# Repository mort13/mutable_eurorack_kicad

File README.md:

Mutable Instruments' Eurorack Modules.

Forked from pichenettes' version and identical except:
- Eagle brd and sch files converted to XML (making possible import into KiCad)
- For some modules, KiCad versions have been added

I have updated this repo to reflect upstream changes, but I am no longer able to convert the Eagle files, so not all are available as XML.

* [Blades](http://mutable-instruments.net/modules/blades): Dual multimode filter.
* [Blinds](http://mutable-instruments.net/modules/blinds): Quad VC-polarizer.
* [Braids](http://mutable-instruments.net/modules/braids): Macro-oscillator.
* [Branches](http://mutable-instruments.net/modules/branches): Dual Bernoulli gate.
* [Clouds](http://mutable-instruments.net/modules/clouds): Texture synthesizer.
* [Ears](http://mutable-instruments.net/modules/ears): Contact microphone.
* [Edges](http://mutable-instruments.net/modules/edges): Quad chiptune digital oscillator.
* [Elements](http://mutable-instruments.net/modules/elements): Modal synthesizer.
* [Frames](http://mutable-instruments.net/modules/frames): Keyframer/mixer.
* [Grids](http://mutable-instruments.net/modules/grids): Topographic drum sequencer.
* [Kinks](http://mutable-instruments.net/modules/kinks): Utility module - rectifier, analog logic, S&H, noise.
* [Links](http://mutable-instruments.net/modules/links): Utility module - buffer, mixer.
* [Marbles](http://mutable-instruments.net/modules/marbles): Random sampler.
* [Peaks](http://mutable-instruments.net/modules/peaks): Dual trigger converter.
* [Plaits](http://mutable-instruments.net/modules/plaits): Macro oscillator.
* [Rings](http://mutable-instruments.net/modules/rings): Resonator.
* [Ripples](http://mutable-instruments.net/modules/ripples): Liquid 2-pole BP, 2-pole LP and 4-pole LP filter.
* [Shades](http://mutable-instruments.net/modules/shades): Triple attenuverter.
* [Shelves](http://mutable-instruments.net/modules/shelves): EQ filter.
* [Stages](http://mutable-instruments.net/modules/stages): Segment generator.
* [Streams](http://mutable-instruments.net/modules/streams): Dual dynamics gate.
* [Tides](http://mutable-instruments.net/modules/tides): Tidal modulator.
* [Veils](http://mutable-instruments.net/modules/veils): Quad VCA.
* [Volts](http://mutable-instruments.net/modules/volts): +5V power module.
* [Warps](http://mutable-instruments.net/modules/warps): Meta-modulator.
* [Yarns](http://mutable-instruments.net/modules/yarns): MIDI interface.

License
=======

Code (AVR projects): GPL3.0.

Code (STM32F projects): MIT license.

Hardware: cc-by-sa-3.0

By: Emilie Gillet (emilie.o.gillet@gmail.com)

Guidelines for derivative works
===============================

**Mutable Instruments is a registered trademark.**

The name "Mutable Instruments" should not be used on any of the derivative works you create from these files.

We do not recommend you to keep the original name of the Mutable Instruments module for your derivative works.

For example, your 5U adaptation of Mutable Instruments Clouds can be called "Foobar Modular - Particle Generator".

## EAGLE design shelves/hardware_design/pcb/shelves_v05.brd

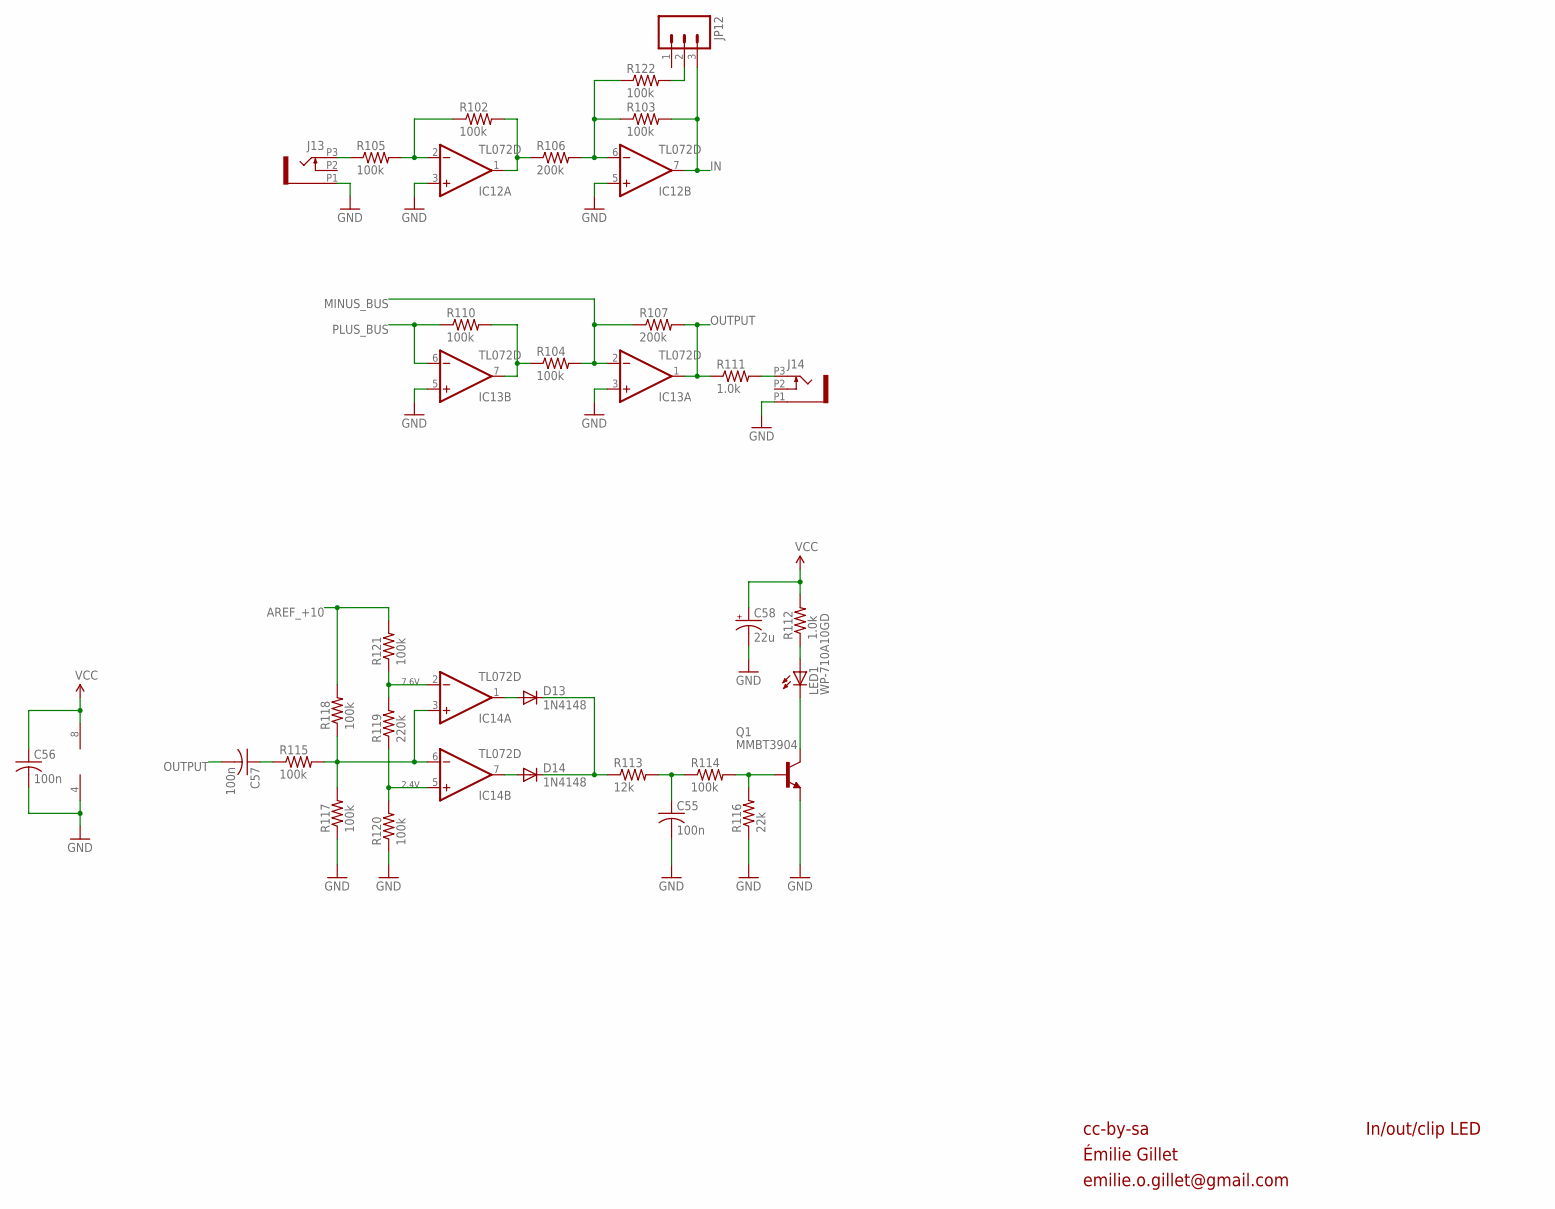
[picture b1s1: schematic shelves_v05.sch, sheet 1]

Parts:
C55, C56, C57: 100n; C0603
C58: 22u; PANASONIC_C
D13, D14: 1N4148; SOD323-W
IC12, IC13, IC14: TL072D; SO08
J13, J14: PJ301_THONKICONN6; WQP_PJ_301M6
JP12: M03PTH; 1X03
LED1: WP-710A10GD; LED3MM
Q1: MMBT3904; SOT23-BEC
R102, R103, R104, R105, R110, R114, R115, R117, R118, R120, R121, R122: 100k; R0603
R106, R107: 200k; R0603
R111, R112: 1.0k; R0603
R113: 12k; R0603
R116: 22k; R0603
R119: 220k; R0603

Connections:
AREF_+10: R118.2, R121.2; also elsewhere on the board
GND: C55.2, C56.2, C58.-, IC12.3 (+IN), IC12.5 (+IN), IC13.3 (+IN), IC13.5 (+IN), IC14.4 (V-), J13.P1 (1), J14.P1 (1), Q1.E, R116.1, R117.1, R120.1; also elsewhere on the board
IN: IC12.7 (OUT), JP12.3, R103.2; also elsewhere on the board
IN_INV: IC12.1 (OUT), R102.2, R106.1
IN_INV1: IC13.7 (OUT), R104.1, R110.2
J_IN: J13.P3 (3), R105.1
MINUS_BUS: IC13.2 (-IN), R104.2, R107.1; also elsewhere on the board
unnamed: JP12.2, R122.2
unnamed: IC12.2 (-IN), R102.1, R105.2
unnamed: IC12.6 (-IN), R103.1, R106.2, R122.1
unnamed: LED1.K (C), Q1.C
unnamed: J14.P3 (3), R111.2
unnamed: C57.1, R115.1
unnamed: IC14.3 (+IN), IC14.6 (-IN), R115.2, R117.2, R118.1
unnamed: IC14.2 (-IN), R119.2, R121.1
unnamed: C55.1, R113.2, R114.1
unnamed: IC14.5 (+IN), R119.1, R120.2
unnamed: D13.A, IC14.1 (OUT)
unnamed: D14.A, IC14.7 (OUT)
unnamed: D13.C, D14.C, R113.1
unnamed: LED1.A, R112.1
unnamed: Q1.B, R114.2, R116.2
OUTPUT: C57.2, IC13.1 (OUT), R107.2, R111.1
PLUS_BUS: IC13.6 (-IN), R110.1; also elsewhere on the board
VCC: C56.1, C58.+, IC14.8 (V+), R112.2; also elsewhere on the board

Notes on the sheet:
cc-by-sa
In/out/clip LED
2.4V
7.6V
Émilie Gillet
emilie.o.gillet@gmail.com

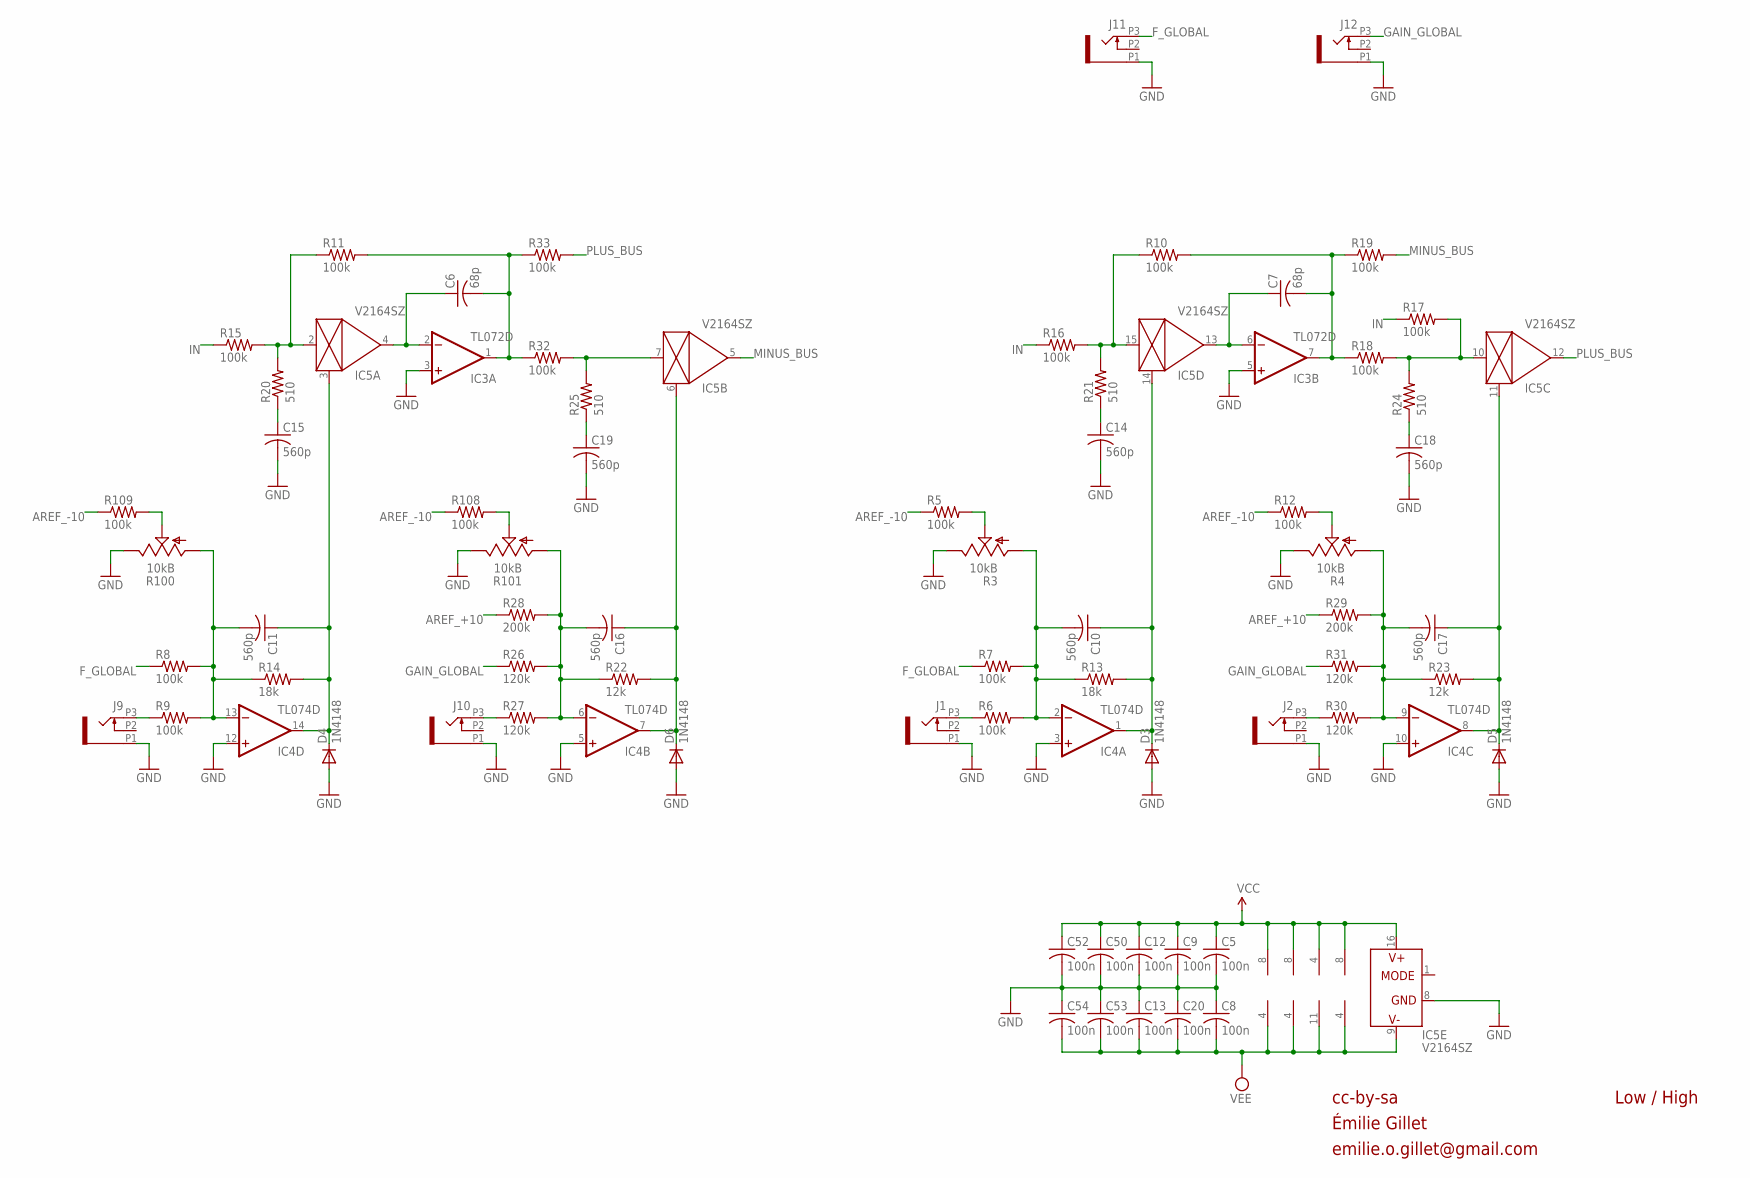
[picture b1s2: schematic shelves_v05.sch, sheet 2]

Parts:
C5, C8, C9, C12, C13, C20, C50, C52, C53, C54: 100n; C0603
C6, C7: 68p; C0603
C10, C11, C14, C15, C16, C17, C18, C19: 560p; C0603
D3, D4, D5, D6: 1N4148; SOD323-W
IC3, IC12, IC13: TL072D; SO08
IC4: TL074D; SO14
IC5: V2164SZ; SOIC16N
J1, J2, J9, J10, J11, J12: PJ301_THONKICONN6; WQP_PJ_301M6
R3, R4, R100, R101: 10kB; ALPS_POT_VERTICAL_PS
R5, R6, R7, R8, R9, R10, R11, R12, R15, R16, R17, R18, R19, R32, R33, R108, R109: 100k; R0603
R13, R14: 18k; R0603
R20, R21, R24, R25: 510; R0603
R22, R23: 12k; R0603
R26, R27, R30, R31: 120k; R0603
R28, R29: 200k; R0603

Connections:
AREF_+10: R28.1, R29.1; also elsewhere on the board
AREF_-10: R5.1, R12.1, R108.1, R109.1; also elsewhere on the board
F_GLOBAL: J11.P3 (3), R7.1, R8.1; also elsewhere on the board
GAIN_GLOBAL: J12.P3 (3), R26.1, R31.1; also elsewhere on the board
GND: C5.2, C8.1, C9.2, C12.2, C13.1, C14.2, C15.2, C18.2, C19.2, C20.1, C50.2, C52.2, C53.1, C54.1, D3.A, D4.A, D5.A, D6.A, IC3.3 (+IN), IC3.5 (+IN), IC4.3 (+IN), IC4.5 (+IN), IC4.10 (+IN), IC4.12 (+IN), IC5.8 (GND), J1.P1 (1), J2.P1 (1), J9.P1 (1), J10.P1 (1), J11.P1 (1), J12.P1 (1), R3.P$1 (E), R4.P$1 (E), R100.P$1 (E), R101.P$1 (E); also elsewhere on the board
IN: R15.1, R16.1, R17.1; also elsewhere on the board
J_HF_CV: J2.P3 (3), R30.1
J_HF_F: J1.P3 (3), R6.1
J_LF_CV: J10.P3 (3), R27.1
J_LF_F: J9.P3 (3), R9.1
LP: C6.2, IC3.1 (OUT), R11.2, R32.1, R33.1
LP1: C7.2, IC3.7 (OUT), R10.2, R18.1, R19.1
MINUS_BUS: IC5.5 (OUT), R19.2; also elsewhere on the board
unnamed: IC5.2 (IN), R11.1, R15.2, R20.2
unnamed: C19.1, R25.1
unnamed: C11.1, D4.C, IC4.14 (OUT), IC5.3 (CTRL), R14.2
unnamed: C6.1, IC3.2 (-IN), IC5.4 (OUT)
unnamed: C14.1, R21.1
unnamed: C16.1, D6.C, IC4.7 (OUT), IC5.6 (CTRL), R22.2
unnamed: C15.1, R20.1
unnamed: R100.P$2 (S), R109.2
unnamed: C16.2, IC4.6 (-IN), R22.1, R26.2, R27.2, R28.2, R101.P$3 (A)
unnamed: R101.P$2 (S), R108.2
unnamed: IC5.15 (IN), R10.1, R16.2, R21.2
unnamed: IC5.7 (IN), R25.2, R32.2
unnamed: C11.2, IC4.13 (-IN), R8.2, R9.2, R14.1, R100.P$3 (A)
unnamed: C7.1, IC3.6 (-IN), IC5.13 (OUT)
unnamed: R3.P$2 (S), R5.2
unnamed: C17.1, D5.C, IC4.8 (OUT), IC5.11 (CTRL), R23.2
unnamed: C17.2, IC4.9 (-IN), R4.P$3 (A), R23.1, R29.2, R30.2, R31.2
unnamed: R4.P$2 (S), R12.2
unnamed: C10.2, IC4.2 (-IN), R3.P$3 (A), R6.2, R7.2, R13.1
unnamed: C18.1, R24.1
unnamed: IC5.10 (IN), R17.2, R18.2, R24.2
unnamed: C10.1, D3.C, IC4.1 (OUT), IC5.14 (CTRL), R13.2
PLUS_BUS: IC5.12 (OUT), R33.2; also elsewhere on the board
VCC: C5.1, C9.1, C12.1, C50.1, C52.1, IC3.8 (V+), IC4.4 (V+), IC5.16 (V+), IC12.8 (V+), IC13.8 (V+); also elsewhere on the board
VEE: C8.2, C13.2, C20.2, C53.2, C54.2, IC3.4 (V-), IC4.11 (V-), IC5.9 (V-), IC12.4 (V-), IC13.4 (V-); also elsewhere on the board

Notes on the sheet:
cc-by-sa
Low / High
Émilie Gillet
emilie.o.gillet@gmail.com

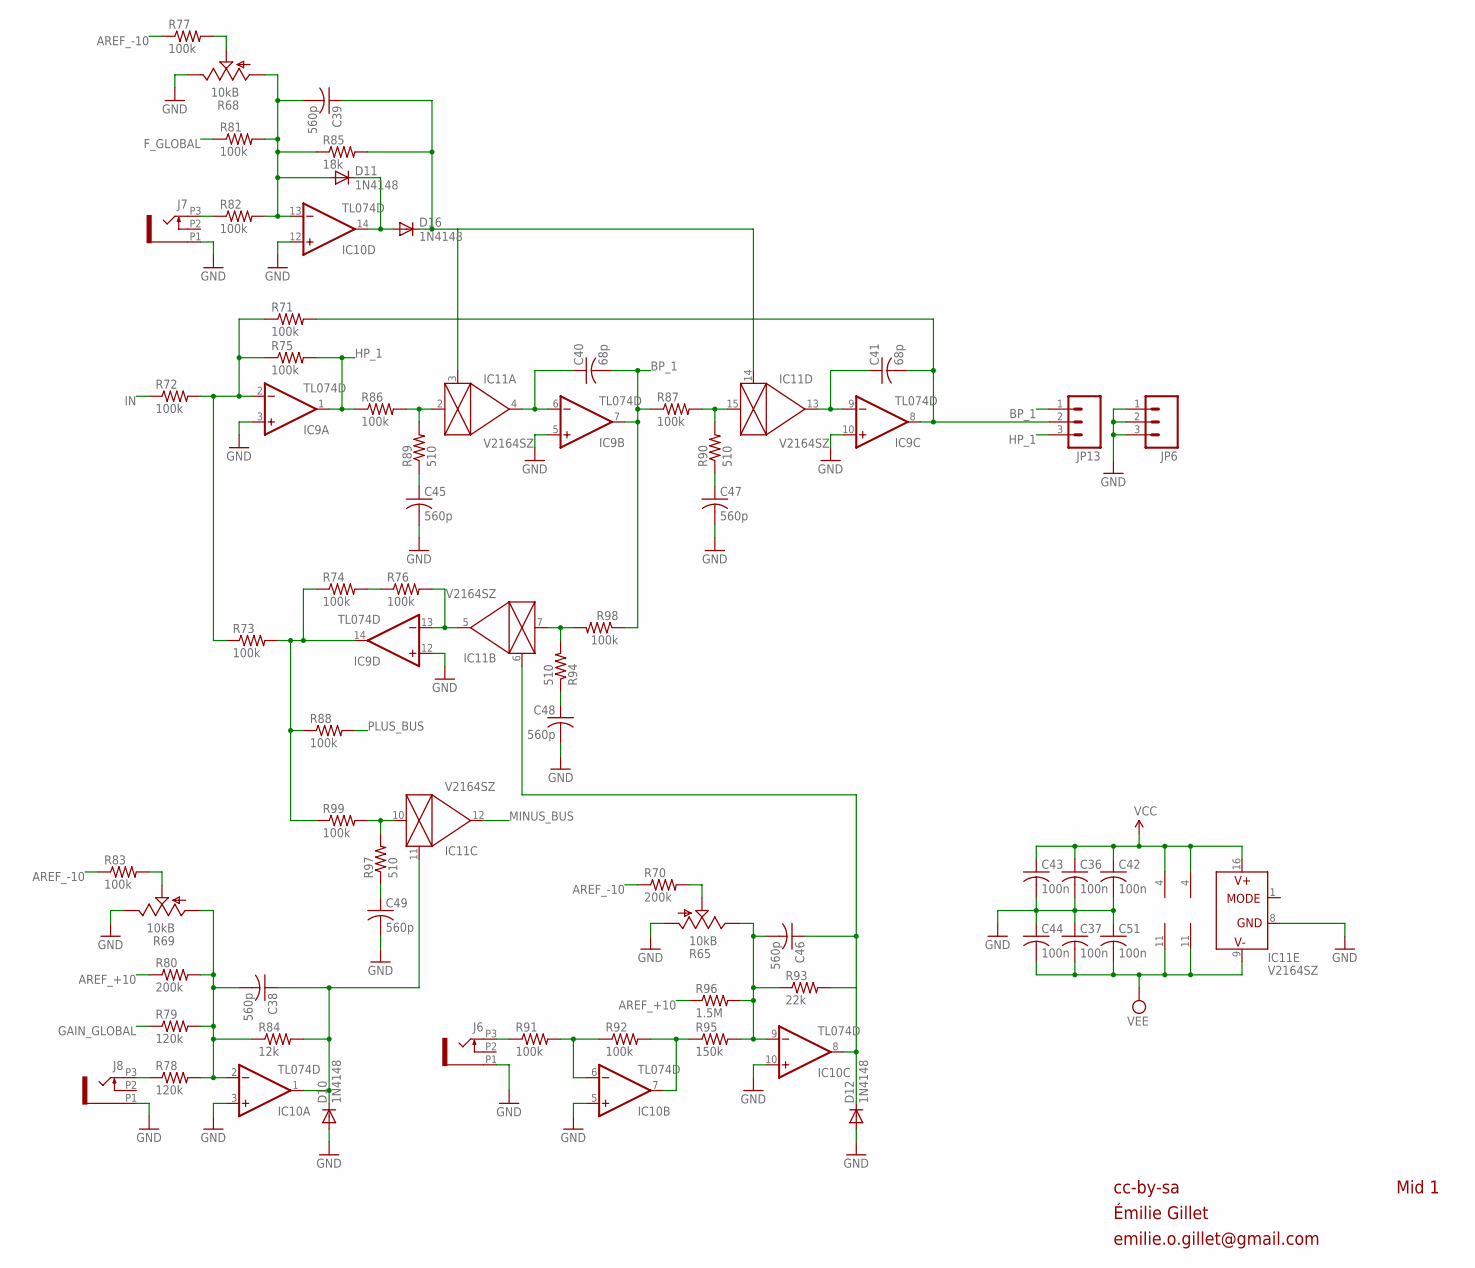
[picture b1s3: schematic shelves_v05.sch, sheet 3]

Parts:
C36, C37, C42, C43, C44, C51: 100n; C0603
C38, C39, C45, C46, C47, C48, C49: 560p; C0603
C40, C41: 68p; C0603
D10, D11, D12, D16: 1N4148; SOD323-W
IC9, IC10: TL074D; SO14
IC11: V2164SZ; SOIC16N
J6, J7, J8: PJ301_THONKICONN6; WQP_PJ_301M6
JP6, JP13: M03PTH; 1X03
R65: 10kB; ALPS_POT_VERTICAL
R68, R69: 10kB; ALPS_POT_VERTICAL_PS
R70, R80: 200k; R0603
R71, R72, R73, R74, R75, R76, R77, R81, R82, R83, R86, R87, R88, R91, R92, R98, R99: 100k; R0603
R78, R79: 120k; R0603
R84: 12k; R0603
R85: 18k; R0603
R89, R90, R94, R97: 510; R0603
R93: 22k; R0603
R95: 150k; R0603
R96: 1.5M; R0603

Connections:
AREF_+10: R80.1, R96.1; also elsewhere on the board
AREF_-10: R70.1, R77.1, R83.1; also elsewhere on the board
BP_1: C40.2, IC9.7 (OUT), JP13.1, R87.1, R98.1
F_GLOBAL: R81.1; also elsewhere on the board
GAIN_GLOBAL: R79.1; also elsewhere on the board
GND: C36.2, C37.1, C42.2, C43.2, C44.1, C45.2, C47.2, C48.2, C49.2, C51.1, D10.A, D12.A, IC9.3 (+IN), IC9.5 (+IN), IC9.10 (+IN), IC9.12 (+IN), IC10.3 (+IN), IC10.5 (+IN), IC10.10 (+IN), IC10.12 (+IN), IC11.8 (GND), J6.P1 (1), J7.P1 (1), J8.P1 (1), JP6.1, JP6.2, JP6.3, R65.P$3 (A), R68.P$1 (E), R69.P$1 (E); also elsewhere on the board
HP_1: IC9.1 (OUT), JP13.3, R75.2, R86.1
IN: R72.1; also elsewhere on the board
MID1_F2: C39.1, D16.C, IC11.3 (CTRL), IC11.14 (CTRL), R85.2
MINUS_BUS: IC11.12 (OUT); also elsewhere on the board
unnamed: D11.C, D16.A, IC10.14 (OUT)
unnamed: IC10.7 (OUT), R92.2, R95.1
unnamed: C45.1, R89.1
unnamed: J7.P3 (3), R82.1
unnamed: R68.P$2 (S), R77.2
unnamed: C38.1, D10.C, IC10.1 (OUT), IC11.11 (CTRL), R84.2
unnamed: C38.2, IC10.2 (-IN), R69.P$3 (A), R78.2, R79.2, R80.2, R84.1
unnamed: J8.P3 (3), R78.1
unnamed: R69.P$2 (S), R83.2
unnamed: C39.2, D11.A, IC10.13 (-IN), R68.P$3 (A), R81.2, R82.2, R85.1
unnamed: C49.1, R97.1
unnamed: IC11.10 (IN), R97.2, R99.2
unnamed: IC9.2 (-IN), R71.1, R72.2, R73.1, R75.1
unnamed: IC11.2 (IN), R86.2, R89.2
unnamed: C40.1, IC9.6 (-IN), IC11.4 (OUT)
unnamed: C47.1, R90.1
unnamed: IC11.15 (IN), R87.2, R90.2
unnamed: C41.1, IC9.9 (-IN), IC11.13 (OUT)
unnamed: C41.2, IC9.8 (OUT), JP13.2, R71.2
unnamed: C48.1, R94.1
unnamed: IC11.7 (IN), R94.2, R98.2
unnamed: IC9.13 (-IN), IC11.5 (OUT), R76.2
unnamed: R74.2, R76.1
unnamed: IC9.14 (OUT), R73.2, R74.1, R88.1, R99.1
unnamed: C46.1, D12.C, IC10.8 (OUT), IC11.6 (CTRL), R93.2
unnamed: C46.2, IC10.9 (-IN), R65.P$1 (E), R93.1, R95.2, R96.2
unnamed: R65.P$2 (S), R70.2
unnamed: J6.P3 (3), R91.1
unnamed: IC10.6 (-IN), R91.2, R92.1
PLUS_BUS: R88.2; also elsewhere on the board
VCC: C36.1, C42.1, C43.1, IC9.4 (V+), IC10.4 (V+), IC11.16 (V+); also elsewhere on the board
VEE: C37.2, C44.2, C51.2, IC9.11 (V-), IC10.11 (V-), IC11.9 (V-); also elsewhere on the board

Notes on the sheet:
cc-by-sa
Mid 1
Émilie Gillet
emilie.o.gillet@gmail.com

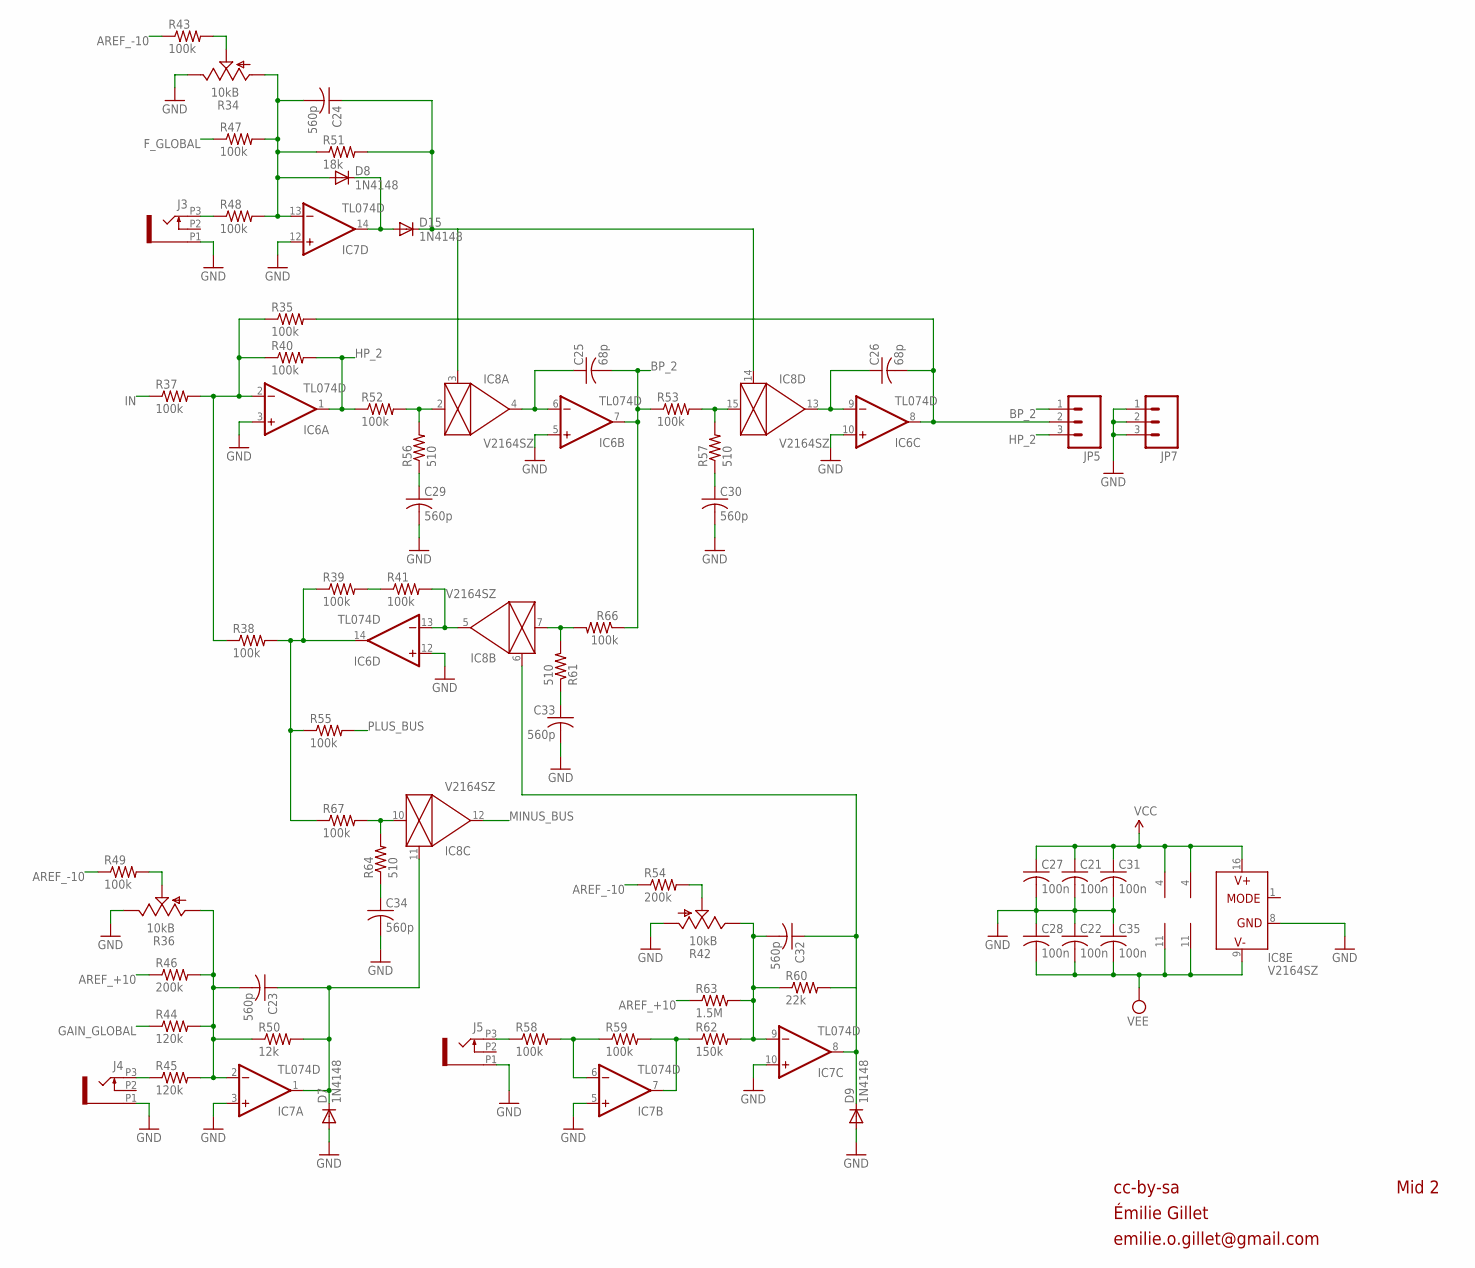
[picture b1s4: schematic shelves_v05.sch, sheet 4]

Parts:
C21, C22, C27, C28, C31, C35: 100n; C0603
C23, C24, C29, C30, C32, C33, C34: 560p; C0603
C25, C26: 68p; C0603
D7, D8, D9, D15: 1N4148; SOD323-W
IC6, IC7: TL074D; SO14
IC8: V2164SZ; SOIC16N
J3, J4, J5: PJ301_THONKICONN6; WQP_PJ_301M6
JP5, JP7: M03PTH; 1X03
R34, R36: 10kB; ALPS_POT_VERTICAL_PS
R35, R37, R38, R39, R40, R41, R43, R47, R48, R49, R52, R53, R55, R58, R59, R66, R67: 100k; R0603
R42: 10kB; ALPS_POT_VERTICAL
R44, R45: 120k; R0603
R46, R54: 200k; R0603
R50: 12k; R0603
R51: 18k; R0603
R56, R57, R61, R64: 510; R0603
R60: 22k; R0603
R62: 150k; R0603
R63: 1.5M; R0603

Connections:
AREF_+10: R46.1, R63.1; also elsewhere on the board
AREF_-10: R43.1, R49.1, R54.1; also elsewhere on the board
BP_2: C25.2, IC6.7 (OUT), JP5.1, R53.1, R66.1
F_GLOBAL: R47.1; also elsewhere on the board
GAIN_GLOBAL: R44.1; also elsewhere on the board
GND: C21.2, C22.1, C27.2, C28.1, C29.2, C30.2, C31.2, C33.2, C34.2, C35.1, D7.A, D9.A, IC6.3 (+IN), IC6.5 (+IN), IC6.10 (+IN), IC6.12 (+IN), IC7.3 (+IN), IC7.5 (+IN), IC7.10 (+IN), IC7.12 (+IN), IC8.8 (GND), J3.P1 (1), J4.P1 (1), J5.P1 (1), JP7.1, JP7.2, JP7.3, R34.P$1 (E), R36.P$1 (E), R42.P$3 (A); also elsewhere on the board
HP_2: IC6.1 (OUT), JP5.3, R40.2, R52.1
IN: R37.1; also elsewhere on the board
MID1_F1: C24.1, D15.C, IC8.3 (CTRL), IC8.14 (CTRL), R51.2
MINUS_BUS: IC8.12 (OUT); also elsewhere on the board
unnamed: D8.C, D15.A, IC7.14 (OUT)
unnamed: C29.1, R56.1
unnamed: IC7.7 (OUT), R59.2, R62.1
unnamed: J3.P3 (3), R48.1
unnamed: R34.P$2 (S), R43.2
unnamed: C23.1, D7.C, IC7.1 (OUT), IC8.11 (CTRL), R50.2
unnamed: C23.2, IC7.2 (-IN), R36.P$3 (A), R44.2, R45.2, R46.2, R50.1
unnamed: J4.P3 (3), R45.1
unnamed: R36.P$2 (S), R49.2
unnamed: C24.2, D8.A, IC7.13 (-IN), R34.P$3 (A), R47.2, R48.2, R51.1
unnamed: C34.1, R64.1
unnamed: IC8.10 (IN), R64.2, R67.2
unnamed: IC6.2 (-IN), R35.1, R37.2, R38.1, R40.1
unnamed: IC8.2 (IN), R52.2, R56.2
unnamed: C25.1, IC6.6 (-IN), IC8.4 (OUT)
unnamed: C30.1, R57.1
unnamed: IC8.15 (IN), R53.2, R57.2
unnamed: C26.1, IC6.9 (-IN), IC8.13 (OUT)
unnamed: C26.2, IC6.8 (OUT), JP5.2, R35.2
unnamed: C33.1, R61.1
unnamed: IC8.7 (IN), R61.2, R66.2
unnamed: IC6.13 (-IN), IC8.5 (OUT), R41.2
unnamed: R39.2, R41.1
unnamed: IC6.14 (OUT), R38.2, R39.1, R55.1, R67.1
unnamed: C32.1, D9.C, IC7.8 (OUT), IC8.6 (CTRL), R60.2
unnamed: C32.2, IC7.9 (-IN), R42.P$1 (E), R60.1, R62.2, R63.2
unnamed: IC7.6 (-IN), R58.2, R59.1
unnamed: R42.P$2 (S), R54.2
unnamed: J5.P3 (3), R58.1
PLUS_BUS: R55.2; also elsewhere on the board
VCC: C21.1, C27.1, C31.1, IC6.4 (V+), IC7.4 (V+), IC8.16 (V+); also elsewhere on the board
VEE: C22.2, C28.2, C35.2, IC6.11 (V-), IC7.11 (V-), IC8.9 (V-); also elsewhere on the board

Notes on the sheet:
cc-by-sa
Mid 2
Émilie Gillet
emilie.o.gillet@gmail.com

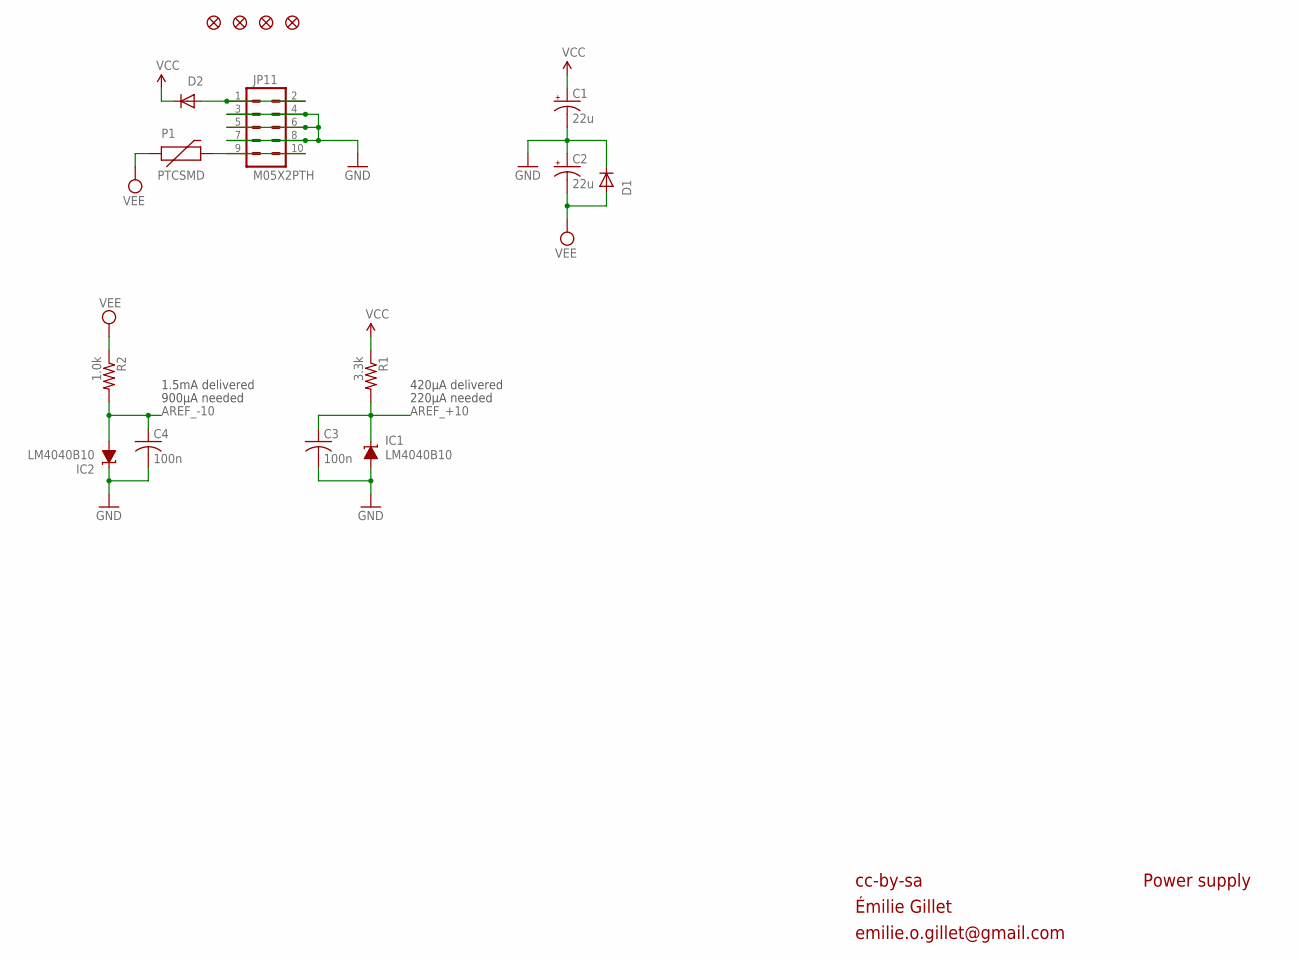
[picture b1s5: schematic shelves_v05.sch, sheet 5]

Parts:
C1, C2: 22u; PANASONIC_C
C3, C4: 100n; C0603
D1, D2: 1N5819HW; SOD123
IC1, IC2: LM4040B10; DBZ_R-PDSO-G3
JP1, JP2, JP3, JP4: FIDUCIAL1X2; FIDUCIAL-1X2
JP11: M05X2PTH; AVR_ICSP
P1: PTCSMD; PTC-1206
R1: 3.3k; R0603
R2: 1.0k; R0603

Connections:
AREF_+10: C3.1, IC1.1 (C), R1.2; also elsewhere on the board
AREF_-10: C4.1, IC2.2 (A), R2.2; also elsewhere on the board
GND: C1.-, C2.+, C3.2, C4.2, D1.C, IC1.2 (A), IC2.1 (C), JP11.3, JP11.4, JP11.5, JP11.6, JP11.7, JP11.8; also elsewhere on the board
unnamed: D2.A, JP11.1, JP11.2
unnamed: JP11.9, JP11.10, P1.2
VCC: C1.+, D2.C, R1.1; also elsewhere on the board
VEE: C2.-, D1.A, P1.1, R2.1; also elsewhere on the board

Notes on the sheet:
cc-by-sa
Power supply
900µA needed
220µA needed
1.5mA delivered
420µA delivered
Émilie Gillet
emilie.o.gillet@gmail.com

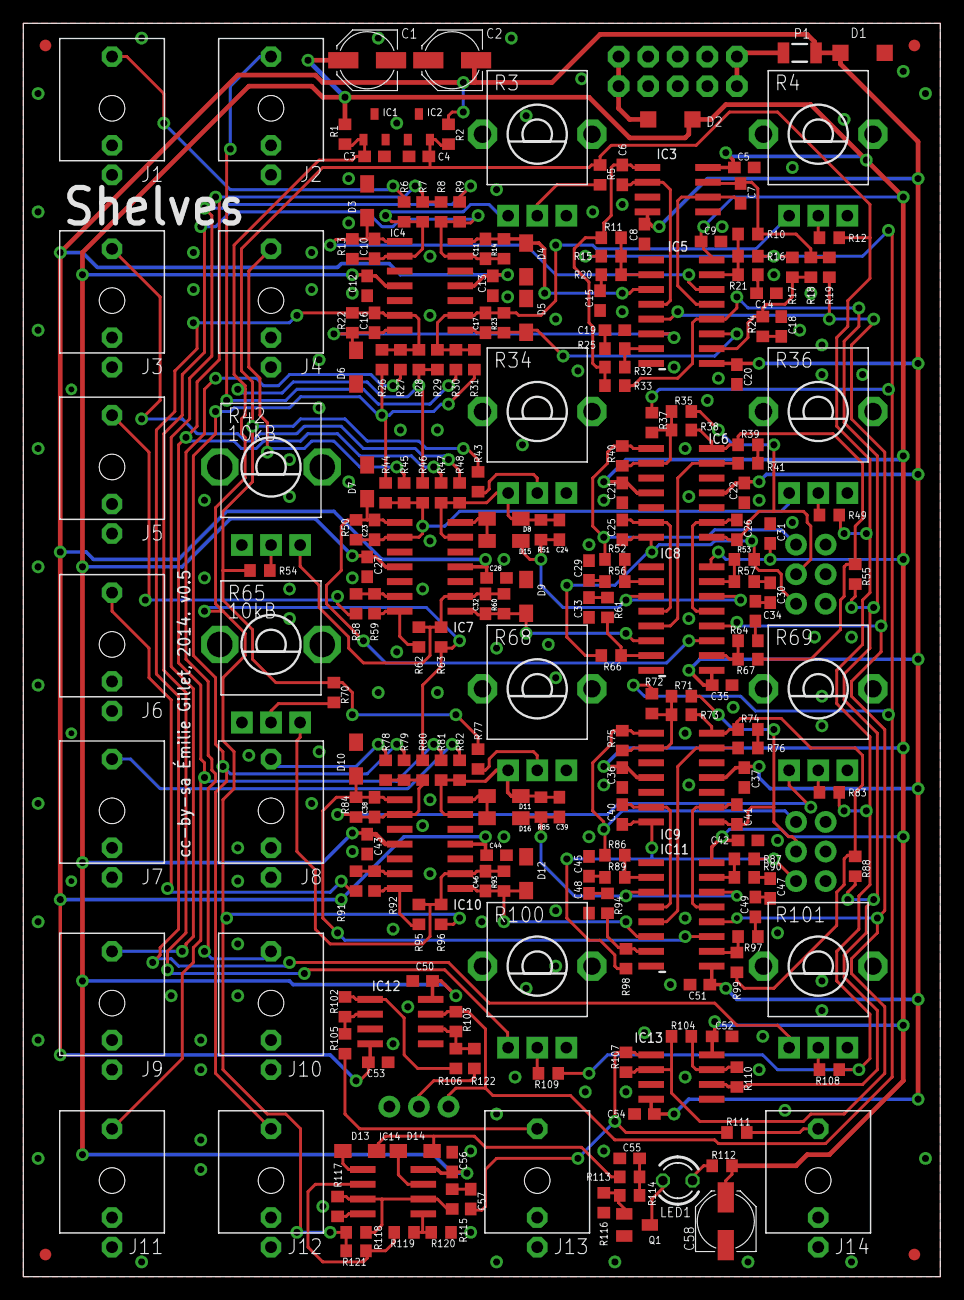
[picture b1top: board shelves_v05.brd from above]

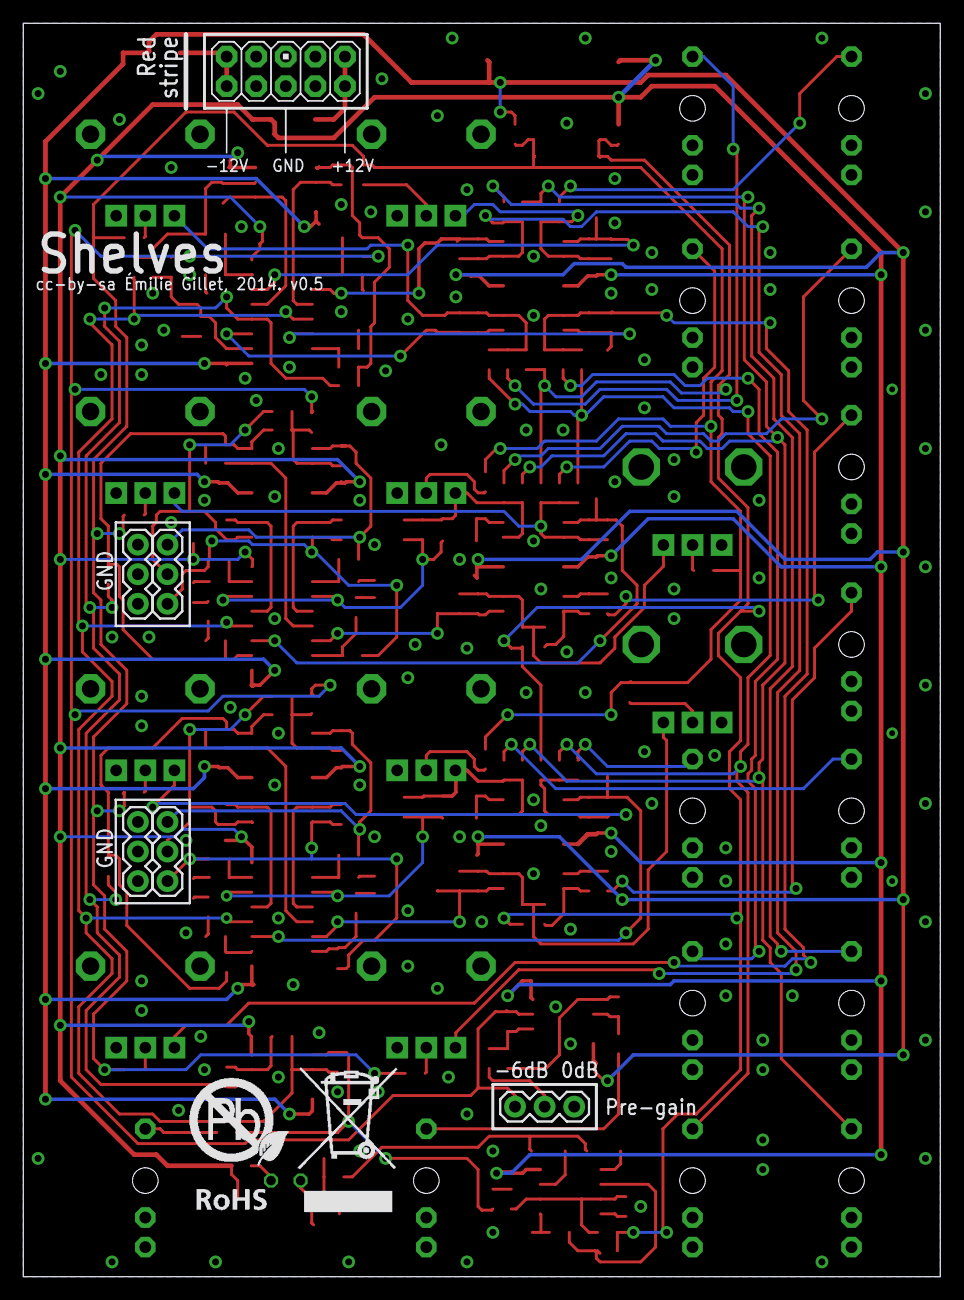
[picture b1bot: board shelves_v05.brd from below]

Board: 2 copper layers, 78.7 x 107.6 mm, 238 parts (7 on the bottom side), 123 nets.

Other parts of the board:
U$2: ROHS_BIG

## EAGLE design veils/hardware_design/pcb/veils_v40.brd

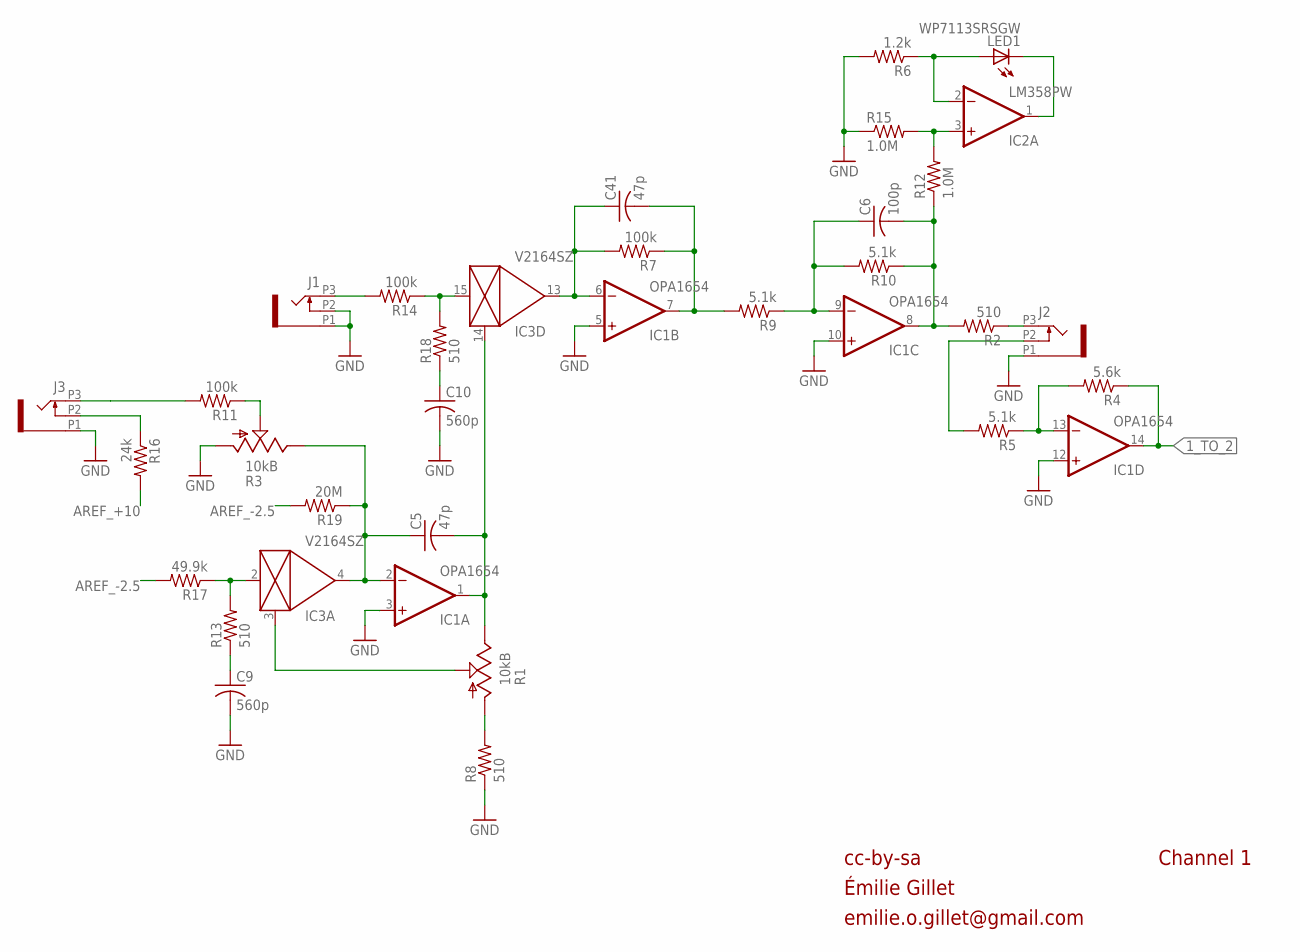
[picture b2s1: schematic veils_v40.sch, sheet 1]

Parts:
C5, C41: 47p; C0402
C6: 100p; C0402
C9, C10: 560p; C0402
IC1: OPA1654; TSSOP14
IC2: LM358PW; TSSOP8
IC3: V2164SZ; SOIC16N
J1, J2, J3: PJ301_THONKICONN6; WQP_PJ_301M6
LED1: WP7113SRSGW; LED5MM
R1: 10kB; ALPS_POT_VERTICAL
R2, R8, R13, R18: 510; R0402
R3: 10kB; ALPS_POT_VERTICAL_PS
R4: 5.6k; R0402
R5, R9, R10: 5.1k; R0402
R6: 1.2k; R0402
R7, R11, R14: 100k; R0402
R12, R15: 1.0M; R0402
R16: 24k; R0402
R17: 49.9k; R0402
R19: 20M; R0402

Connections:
1_TO_2: IC1.14 (OUT), R4.1; also elsewhere on the board
AREF_+10: R16.2; also elsewhere on the board
AREF_-2.5: R17.2, R19.2; also elsewhere on the board
CV_IN_1: J3.P3 (3), R11.2
FOO: IC3.2 (IN), R13.2, R17.1
GND: C9.2, C10.2, IC1.3 (+IN), IC1.5 (+IN), IC1.10 (+IN), IC1.12 (+IN), J1.P1 (1), J1.P2 (2), J2.P1 (1), J3.P1 (1), R3.P$3 (A), R6.2, R8.1, R15.1; also elsewhere on the board
unnamed: IC2.3 (+IN), R12.2, R15.2
unnamed: J2.P3 (3), R2.1
unnamed: IC3.3 (CTRL), R1.P$2 (S)
unnamed: C6.1, IC1.9 (-IN), R9.1, R10.2
unnamed: R3.P$2 (S), R11.1
unnamed: R1.P$3 (A), R8.2
unnamed: IC2.1 (OUT), LED1.K (C)
unnamed: IC2.2 (-IN), LED1.A, R6.1
unnamed: C9.1, R13.1
unnamed: J3.P2 (2), R16.1
unnamed: IC1.13 (-IN), R4.2, R5.1
unnamed: J2.P2 (2), R5.2
unnamed: C10.1, R18.1
unnamed: C5.1, IC1.2 (-IN), IC3.4 (OUT), R3.P$1 (E), R19.1
unnamed: J1.P3 (3), R14.2
unnamed: IC3.15 (IN), R14.1, R18.2
unnamed: C5.2, IC1.1 (OUT), IC3.14 (CTRL), R1.P$1 (E)
unnamed: C41.1, IC1.6 (-IN), IC3.13 (OUT), R7.2
unnamed: C41.2, IC1.7 (OUT), R7.1, R9.2
OUT1: C6.2, IC1.8 (OUT), R2.2, R10.1, R12.1

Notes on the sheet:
cc-by-sa
Channel 1
Émilie Gillet
emilie.o.gillet@gmail.com
